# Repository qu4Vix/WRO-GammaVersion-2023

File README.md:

# WRO 2023 GammaVersion's
**GammaVersion's repo for WRO Future Engineers 2023 season**

***

## Contents

* [Hardware](#hardware)
    * [Components](#component-list)
    * [Models](#models)
    * [Electronics](#electronics)
    * [Ackerman's](#ackerman-steering-geometry)

* [Software](#software)
    * [Sensors](#sensors)
    * [Position](#position)
    * [Strategy](#strategy)

* [Photos](#photos)
    * [Car images](#car-images)
    * [Team images](#team-images)

* [Videos](#videos)
    * [Demonstration videos](#demonstration-videos)

* [Legal](#legal)
    * [License](#license)
    * [Credits](#credits)

***

## Hardware
Building an autonomous car for this challenge involves a meticulous process of reimagining and redesigning various components to achieve precision, safety, and efficiency. In this project, we focused on enhancing the car's steering mechanism, designing a custom-printed circuit board (PCB) to connect all the components seamlessly, and implementing Light Detection and Ranging (LiDAR) technology for superior distance measurement compared to traditional ultrasonic sensors.

### Component List
* **DOIT ESP32 DevKit V1 x2**
* **Pixy 2**
* **RPLIDAR A1 M8**
* **MPU 9250**
* **Pololu Magnetic Encoder**
* **DSM44 Servo**
* **RC Smart Car Chassis Kit** Includes a simple motor
* **Motor Driver x2**
* **Power Supply x3**
* **RGB LEDS**

### Models
**3D-Printed Supports and Structural Parts:**
As a crucial part of our project, we designed and 3D-printed custom supports to secure mechanical components and sensors. These supports ensured precise placement and minimized interference. Additionally, we utilized 3D printing to create lightweight yet robust structural components, allowing us to tailor the car's design to our specific needs while maintaining its strength and adaptability.

### Electronics
**LiDAR Implementation:**
Rather than relying on traditional ultrasonic sensors for obstacle detection, we opted for LiDAR technology. LiDAR, which stands for Light Detection and Ranging, uses laser beams to measure distances to objects with exceptional precision. This technology offers several advantages over ultrasonic sensors:

a. Greater Range: LiDAR can detect objects at much greater distances, providing the car with more time to react to potential obstacles.

b. High Precision: LiDAR provides accurate distance measurements, resulting in better navigation and collision avoidance.

c. 360-Degree Coverage: LiDAR offers a full 360-degree view around the car, ensuring comprehensive situational awareness.

d. Environmental Adaptability: LiDAR is less affected by environmental factors such as ambient light, making it more reliable in various conditions.

**Esp-32**
To bring our autonomous car project to fruition, we opted for the ESP-32 microcontroller as the central control unit. The ESP-32 boasts several compelling advantages that played a pivotal role in our decision-making process:

1. Computing Power and Versatility: The ESP-32 distinguishes itself with its robust computational capabilities and remarkable versatility. Equipped with a potent dual-core processor and ample memory capacity, it emerged as the natural choice for our robotics endeavor, enabling rapid computation and accommodating our storage needs seamlessly.

2. Advanced Wireless Connectivity: The ESP-32 integrates cutting-edge Wi-Fi and Bluetooth connectivity, positioning it as a frontrunner for efficient wireless communication. This capability empowered us to establish seamless and reliable communication channels between the autonomous car and external devices, such as remote controls or monitoring systems.

3. Sensor and Actuator Compatibility: The ESP-32's adaptability extends to sensor and actuator integration. With its multitude of I/O (input/output) pins and versatile interface options, we effortlessly connected and controlled various sensors, including the IMU and LiDAR, as well as the steering servos.

**Custom PCB Design:**
To seamlessly connect and control all the components of our autonomous car, we designed and printed a custom PCB. The PCB acted as the central hub that allowed us to interface with sensors, motors, microcontrollers, and other electronic components efficiently.

Our custom PCB design allowed for cleaner wiring, reduced interference, and enhanced reliability. It simplified the process of connecting and configuring various sensors and actuators, enabling smoother integration and troubleshooting during the development phase.

Our custom-designed PCB played a central role in integrating various components seamlessly. To ensure efficient power management and distribution, we implemented three distinct power sources:

a. Dual 5-Volt Power Supplies: One 5-volt power supply was dedicated to powering the LiDAR system, while the other supplied power to the steering servos. This separation of power sources allowed us to optimize the energy delivery to these critical components, ensuring their reliable operation.
<div calss ="row">
    <div class="column"></div>
    <div class="column"></div>
</div>

b. 3.3-Volt Power Supply: A dedicated 3.3-volt power supply was employed to energize the microcontrollers, IMU (Inertial Measurement Unit), motor drivers, and LED lights. This voltage level was carefully chosen to meet the requirements of these electronic components, guaranteeing stable and consistent performance.

By employing these distinct power sources, we effectively managed the power needs of our autonomous car's various subsystems, ensuring that each component received the appropriate voltage and current for reliable operation. This meticulous power management contributed to the overall success and stability of our robotics project.

### Ackerman's Steering Geometry
One of the key aspects of our project was reimagining the steering system to achieve a reduced turn ratio. To accomplish this, we implemented Ackermann steering geometry. Ackermann steering geometry is a mechanism that ensures that all four wheels of the car track along different paths during a turn, reducing tire wear and enabling smoother and more precise turns.

By incorporating Ackermann steering, we were able to optimize the car's turning radius, allowing it to navigate tighter corners with ease. This was achieved by adjusting the angles of the wheels and their pivot points, ensuring that the inner and outer wheels followed distinct paths, greatly enhancing the car's maneuverability.

***

## Software

### Sensors
* **MPU:** We use the MPU's GyroScope functionality to measure the angular speed along the Z-axis. Integrating this speed over time we get the orientation of the car.
* **Encoder:** The encoder allows us to know the displacement of the car and consequently its speed, which we regulate using a PID controller.
* **LIDAR:** The LIDAR sensor measures distances on a 360º range, therefore it allows the car to have a great knowledge of the surroundings. We store all the readings in an array when they are received.
* **Pixy 2:** Pixy is an intelligent camera which can identify regions with the same colour. As a result, our code to handle the detection of the traffic lights is very reduced. 

### Position
With the data of the orientation and the displacement of the car we are able to calculate the position of the car. This is worked out by integrating the displacement over the trajectory of the car. With these calculations the coordiante origin is set to the initial position of the car, but we change it to the bottom left corner of the playfield with the measures of the LIDAR.

### Strategy
Our strategy is to make the car able to define a path for the it to follow depending on the colour blocks it detects. We devide the playfield into eight sections, and the car stores whether it has to travel to the right or to the left in each section.

***

## Photos

### Car images
| | |
| ------------------------- | ------------------------- |
|  |  |
|  |  |
|  |  |

### Team images
| | |
| ------------------------- | ------------------------- |
|  |  |

***

## Videos

### Demonstration videos

Demonstration videos of the car successfully completing both challenges.
The links to each of them can be found in:
* [Open Challenge](https://youtu.be/Oyp9x_MhnpQ?si=n7GRa3e0AN-YdxIk)
* [Obstacle Challenge](https://youtu.be/bCaAXYcNQ1c)

***

## Legal

### License

The [source code](/code/) in this repository is licensed under the **GNU General Public License v3.0**.

The [hardware](/robot-info/hardware/) exposed in this project is licensed under the **Creative Commons Attribution Share Alike 4.0 International** license.

The documentation of this repository; found in [`robot-info`](/robot-info/), [`vehicle-photos`](/vehicle-photos/), [`videos`](/videos/), [`team-photos`](/team-photos/), as well as this `README.md`; is licensed under the **CERN Open Hardware Licence Version 2 - Strongly Reciprocal** license.

A copy of each license can be found in the [LICENSE](LICENSE) file. More information about the licenses in the specific README.md of each section.

### Credits

***

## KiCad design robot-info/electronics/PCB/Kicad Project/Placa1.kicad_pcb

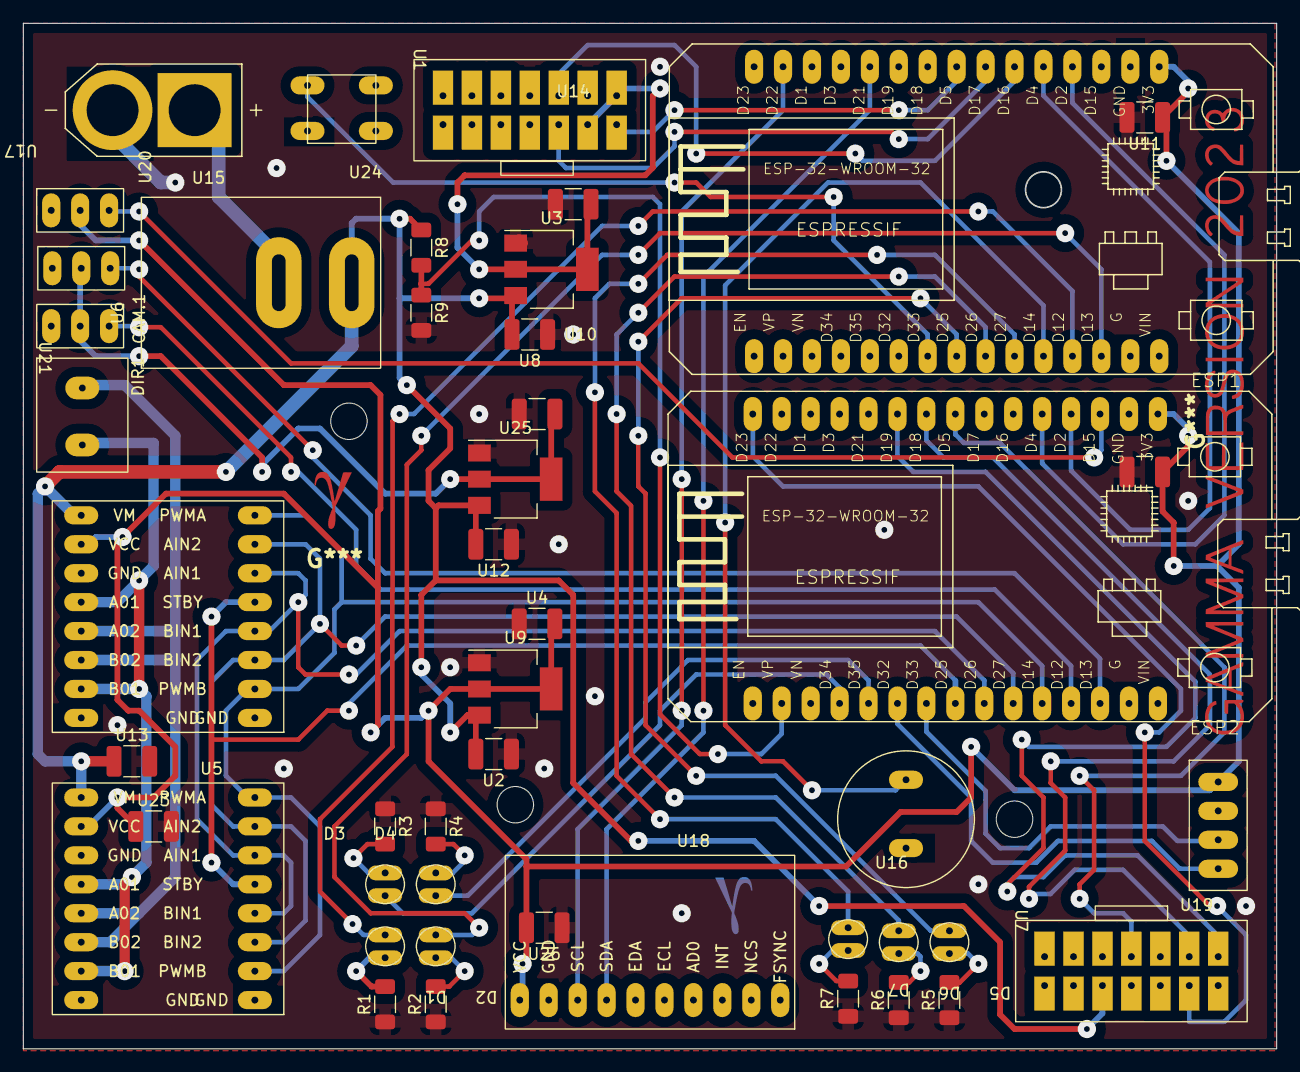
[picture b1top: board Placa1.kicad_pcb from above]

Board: 2 copper layers, 110.0 x 90.0 mm, 46 parts (0 on the bottom side), 45 nets.

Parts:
CAM.1: Servo
D1, D2, D3, D4, D5, D6, D7: LED
DIR1: Servo
ESP1, ESP2: ESP-32; ESP32-DEVKITV1Si
R1, R2, R3, R4, R5, R6, R7, R8, R9: R_US; R_1206_3216Metric_Pad1.30x1.75mm_HandSolder
U1: LIDAR; Lidar
U2, U4, U8, U10, U11, U12, U13, U14, U22, U23, U26: 1210; C_1210_3225Metric_Pad1.33x2.70mm_HandSolder
U3, U9, U25: LM317_SOT-223; SOT-223-3_TabPin2
U5, U6: TB6612FNG
U7: Camara
U15: Bateria; AMASS_XT60-M
U16: Buzzer
U17: Switch
U18: MPU-92-65
U19: Encoder
U20: Tira_Leds; Tira
U21: Motor
U24: Pulsador

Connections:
+3.3V: ESP1.1 (3V), ESP2.1 (3V), U4.2, U5.2 (VCC), U6.2 (VCC), U9.3 (VO), U11.1, U18.1 (VCC), U19.1 (3.3V), U20.1 (3.3V), U22.1, U23.1, U26.2
+5V: CAM.1.1 (5V), DIR1.1 (5V), U10.2, U25.3 (VO)
+7.5V: R8.1, U2.2, U3.1 (VI), U5.1 (VM), U6.1 (VM), U7.6 (VIN), U8.2, U9.1 (VI), U12.2, U13.1, U17.2, U25.1 (VI)
GND: CAM.1.2 (GND), DIR1.2 (GND), ESP1.2 (GND), ESP1.29 (GND), ESP2.2 (GND), ESP2.29 (GND), R1.1, R2.1, R3.1, R4.1, R5.1, R6.1, R7.1, R9.2, U1.3 (GND.M), U1.7 (GND), U2.1, U3.2 (ADJ), U4.1, U5.8 (GND), U5.17 (GND), U6.8 (GND), U6.17 (GND), U7.5 (GND), U8.1, U9.2 (ADJ), U10.1, U11.2, U12.1, U13.2, U14.1, U15.N, U16.2 (GND), U18.2 (GND), U19.2 (GND), U20.2 (GND), U22.2, U23.2, U24.2, U25.2 (ADJ), U26.1
unnamed: CAM.1.3 (S), ESP2.28 (D13)
unnamed: D1.1 (K), R1.2
unnamed: D1.2 (A), ESP1.27 (D12)
unnamed: D2.1 (K), R2.2
unnamed: D2.2 (A), ESP1.28 (D13)
unnamed: D3.1 (K), R3.2
unnamed: D3.2 (A), ESP2.19 (D34)
unnamed: D4.1 (K), R4.2
unnamed: D4.2 (A), ESP2.20 (D35)
unnamed: D5.1 (K), R5.2
unnamed: D5.2 (A), ESP1.23 (D25)
unnamed: D6.1 (K), R6.2
unnamed: D6.2 (A), ESP1.24 (D26)
unnamed: D7.1 (K), R7.2
unnamed: D7.2 (A), ESP1.25 (D27)
unnamed: DIR1.3 (S), ESP2.27 (D12)
unnamed: ESP1.4 (D2), ESP2.5 (D4)
unnamed: ESP1.5 (D4), ESP2.4 (D2)
unnamed: ESP1.6 (D16), U1.5 (TX)
unnamed: ESP1.7 (D17), U1.6 (RX)
unnamed: ESP1.8 (D5), U1.2 (C.MOTOR)
unnamed: ESP1.11 (D21), U18.4 (SDA)
unnamed: ESP1.14 (D22), U18.3 (SCL)
unnamed: ESP1.22 (D33), U24.1
unnamed: ESP1.26 (D14), U16.1 (+)
unnamed: ESP2.3 (D15), U20.3 (S)
unnamed: ESP2.8 (D5), U7.4 (SS)
unnamed: ESP2.9 (D18), U7.3 (SCK)
unnamed: ESP2.10 (D19), U7.1 (MISO)
unnamed: ESP2.15 (D23), U7.2 (MOSI)
unnamed: ESP2.17 (VP), R8.2, R9.1
unnamed: ESP2.21 (D32), U19.4 (S2)
unnamed: ESP2.22 (D33), U19.3 (S1)
unnamed: ESP2.23 (D25), U5.13 (STBY), U6.13 (STBY)
unnamed: ESP2.24 (D26), U5.11 (AIN1), U5.14 (BIN1), U6.11 (AIN1), U6.14 (BIN1)
unnamed: ESP2.25 (D27), U5.10 (AIN2), U5.15 (BIN2), U6.10 (AIN2), U6.15 (BIN2)
unnamed: ESP2.26 (D14), U5.9 (PWMA), U5.16 (PWMB), U6.9 (PWMA), U6.16 (PWMB)
unnamed: U1.1 (5V.M), U1.4 (5V), U3.3 (VO), U14.2
unnamed: U15.P, U17.1
unnamed: U5.5 (A02), U5.6 (B02), U6.5 (A02), U6.6 (B02), U21.1
unnamed: U5.4 (A01), U5.7 (B01), U6.4 (A01), U6.7 (B01), U21.2

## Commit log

2023-02-11 LIDAR info
2023-02-11 LIDAR info - fix
2023-02-11 LIDAR info 2
2023-04-09 Base code projects added
    Projects for a principal ESP32 (Master) and a secondary ESP32 (Slave)
2023-04-09 Motor library created
    Not finished, first sketch
    README, Motor.h and Motor.cpp files
    Inspired in the 2022 version
2023-04-09 Motor changes
    Added keywords
    Simple README
    Perfections to the code
2023-04-09 Servo library created
    Simple skecth of the Servo library
2023-04-10 Encoder library created
    Sketch of the library to control an encoder
2023-04-18 MPU library created
    Library to control a mpu
2023-04-19 Uploaded Simple Electronic Schematic
    Just a conceptual schemetic to obtain a simple idea of the circuit.
2023-04-19 OTA Update library created
    library for updating the code via wifi
    .h + .cpp file
    README.md
    keywords.txt
2023-04-19 Corrections
    ESP32 Slave platform.ini: lib_ldf_mode set to deep
    MPU: Corrections to the measurement
    Motor: Formating
    OTA README: API Reference
2023-04-22 UpdateOTA library updates
    Platform ini: added lib_ignores
    Example file, libary properties and LICENSE added
    Changes to the README: references to third party libraries
    OTAUpdate.h and .cpp: copyright notices, getServer method and some comments for the code
2023-04-22 Update README.md
    General sketch
2023-04-22 Update README.md
    Links in the index
2023-04-22 Added lidar datasheet
2023-05-08 Licensing
2023-06-11 ESP32 Master First code
    Telemetry library created (Not finished)
    OTAUpdate library included
    Pin assignations declared
    lidar, mpu and ota test
2023-06-11 ESP32 Slave First Code
    Pin assignations delcared
    Encoder test
    Motor, servo and ota test
    battery tension test
2023-06-15 Update models
2023-06-23 ESP 32 updates
    gitignore updated
    pinAssignments.h created
    telemetry extended
    otaUpdate: static ip created
    README created
    main updated:
2023-06-23 ESP32 Slave Updated
    gitignore updated
    pinAssignments.h created
    Encoder library: getEncoder method added
    otaUpdate library: staticIP method added
    README.md created
    main.cpp updated:
2023-07-14 Stage 1 almost complete
2023-07-14 Intento del giro
2023-07-21 Update
    Slave: Encoder sending rate higher
2023-07-25 ESP32 Telemetry updated
2023-07-27 26-7-2023
2023-09-04 4-9-2023
2023-09-05 Update Master
2023-09-05 5-9-2023 13:42
2023-09-05 New readLecture function
2023-09-05 5-9-2023 19:40
2023-09-05 Phase 1 completed
2023-09-06 Main code commented
2023-09-06 Folders moved
2023-09-06 Wheel vibration solved
2023-09-06 ESP32 Master Obstacles created
    Project for phase 2 created.
    Copied from Phase 1.
2023-09-06 ESP32 Master Obstacles created
    Project for phase 2 created.
2023-09-06 Pixy library included
2023-09-07 Telemetry corrected
2023-09-07 7-9-2023 10:43
2023-09-07 Camera added to ESP32 Slave
2023-09-07 07/09/2023 14:30
2023-09-07 Pre set turns working
2023-09-07 Fotografias
2023-09-07 Pixy filters size
2023-09-07 7-9-2023 20:07
2023-09-07 Text update
2023-09-07 Revert "7-9-2023 20:07"
    This reverts commit 845503dcec27ac46d311f6a57b603cb1a1d1470b.
2023-09-07 Documentation update
    Added Unity telemetry project.
    Added video demonstration urls.
    models and electronics moved to hardware.
2023-09-07 07/09/2023 21:00
    Phase 2 almost completed.
    Camera detects color blocks.
    Car follows paths.
2023-09-07 Team photos uploaded
2023-09-08 Telemetry updated
    Added section number and section blocks
2023-09-08 08/09/2023 14:21
2023-09-08 Readme updated
2023-09-08 Readme test
2023-09-08 Readme test2
2023-09-08 readme test3
2023-09-08 images
2023-09-08 Readme
2023-09-08 8520
2023-09-08 Nice looking picture chart
2023-09-08 photos edited
2023-09-08 PHASE 2 OBSTACLES AVOIDED
2023-09-09 README
    Software and demonstration videos
2023-09-09 README
    Components
2023-09-09 added track constants
2023-09-10 Presentation video link updated
2023-09-11 Phase 2 clockwise
2023-09-12 12/09/2023 Phase 2 completed
    Third Lap Turn Achieved
2023-09-13 Phase 1 Finiquitada
2023-09-13 camera support
2023-09-13 Final updates
2023-09-13 Telemetry final
2023-09-16 16/09/2023 17:26
    Access point & telemetry fix
    Music for some reason
